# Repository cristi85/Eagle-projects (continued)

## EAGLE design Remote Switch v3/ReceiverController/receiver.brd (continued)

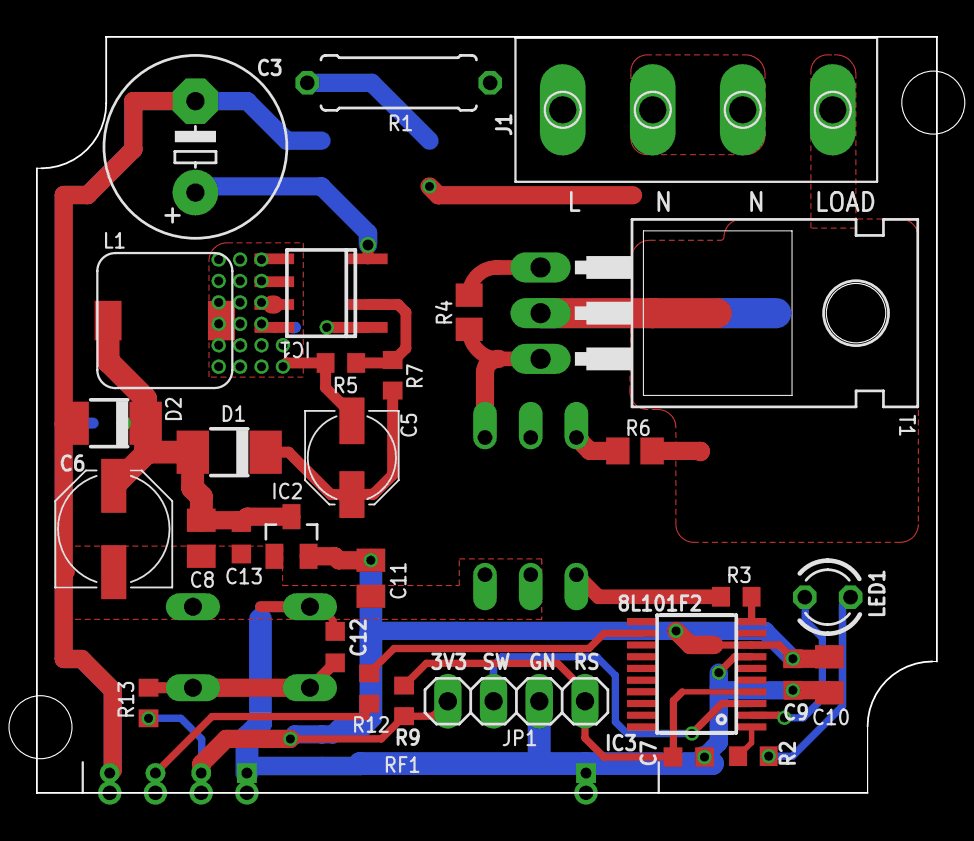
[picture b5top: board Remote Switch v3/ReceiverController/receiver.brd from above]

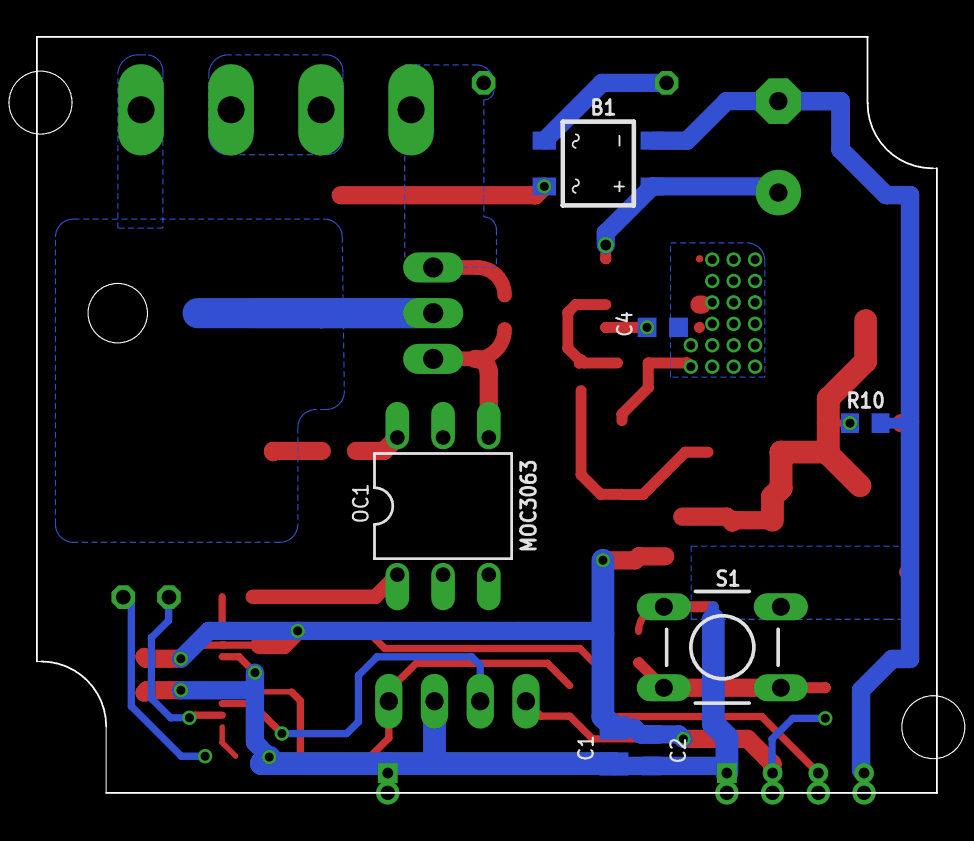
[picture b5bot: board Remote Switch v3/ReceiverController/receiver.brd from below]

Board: 2 copper layers, 50.0 x 42.0 mm, 38 parts (8 on the bottom side), 24 nets.

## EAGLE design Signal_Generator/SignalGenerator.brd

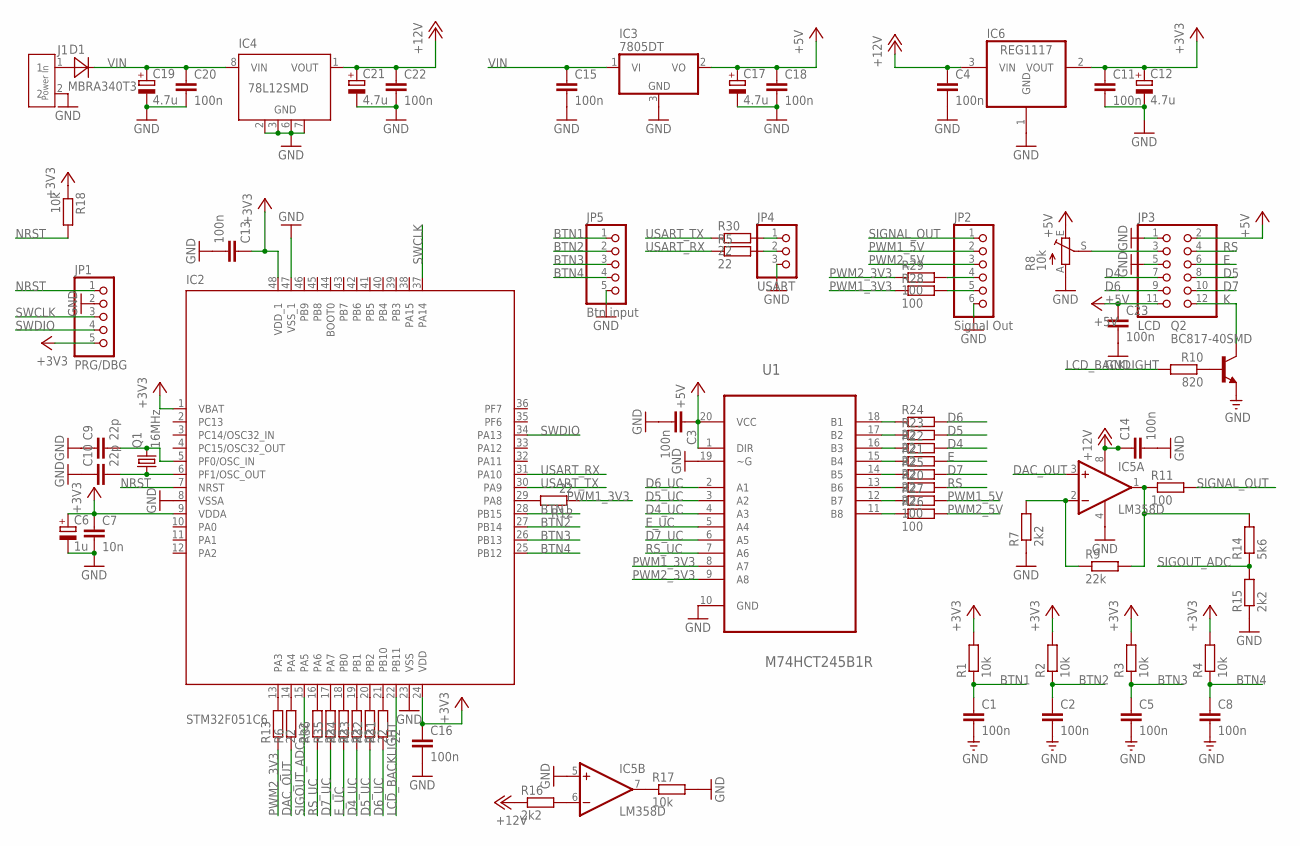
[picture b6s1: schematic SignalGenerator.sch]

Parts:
C1, C2, C3, C4, C5, C8, C11, C13, C14, C15, C16, C18, C20, C22, C23: 100n; C0805
C6: 1u; A/3216-18W
C7: 10n; C0805
C9, C10: 22p; C0603
C12, C21: 4.7u; PANASONIC_A
C17, C19: 4.7u; PANASONIC_B
D1: MBRA340T3; SMA
IC2: STM32F051C6; LQFP48-7X7
IC3: 7805DT; TO252
IC4: 78L12SMD; SO08
IC5: LM358D; SO08
IC6: REG1117; SOT223
J1: Power In; 2P-5.08
JP1: PRG/DBG; 1X05
JP2: Signal Out; 1X06
JP3: LCD; 2X06
JP4: USART; 1X03
JP5: Btn input; 1X05
Q1: 16MHz; SMD_CRYSTAL
Q2: BC817-40SMD; SOT23-BEC
R1, R2, R3, R4, R17, R18: 10k; R0603
R5, R12, R13, R20, R21, R22, R23, R24, R25, R30, R31, R32, R33, R34, R35, R36: 22; R0603
R6, R7, R15, R16: 2k2; R0603
R8: 10k; B25P
R9: 22k; R0603
R10: 820; R0603
R11, R26, R27, R28, R29: 100; R0603
R14: 5k6; R0603
U1: M74HCT245B1R; DIP254P762X393-20

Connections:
+3V3: C6.+, C7.1, C11.1, C12.+, C13.1, C16.1, IC2.1 (VBAT), IC2.9 (VDDA), IC2.24 (VDD), IC2.48 (VDD_1), IC6.2 (VOUT), JP1.5, R1.2, R2.2, R3.2, R4.2, R18.1
+5V: C3.1, C17.+, C18.1, C23.1, IC3.2 (VO), JP3.2, JP3.11, R8.E, U1.1 (DIR), U1.20 (VCC)
+12V: C4.1, C14.1, C21.+, C22.1, IC4.1 (VOUT), IC5.8 (V+), IC6.3 (VIN), R16.1
BTN1: C1.1, IC2.28 (PB15), JP5.1, R1.1
BTN2: C2.1, IC2.27 (PB14), JP5.2, R2.1
BTN3: C5.1, IC2.26 (PB13), JP5.3, R3.1
BTN4: C8.1, IC2.25 (PB12), JP5.4, R4.1
D4: JP3.7, R22.2
D4_UC: R33.1, U1.4 (A3)
D5: JP3.8, R23.2
D5_UC: R32.1, U1.3 (A2)
D6: JP3.9, R24.2
D6_UC: R31.1, U1.2 (A1)
D7: JP3.10, R25.2
D7_UC: R35.1, U1.6 (A5)
DAC_OUT: IC5.3 (+IN), R6.1
E: JP3.6, R21.2
E_UC: R34.1, U1.5 (A4)
GND: C1.2, C2.2, C3.2, C4.2, C5.2, C6.-, C7.2, C8.2, C9.1, C10.1, C11.2, C12.-, C13.2, C14.2, C15.2, C16.2, C17.-, C18.2, C19.-, C20.2, C21.-, C22.2, C23.2, IC2.8 (VSSA), IC2.23 (VSS), IC2.47 (VSS_1), IC3.3 (GND), IC4.2 (GND), IC4.3 (GND), IC4.6 (GND), IC4.7 (GND), IC5.4 (V-), IC5.5 (+IN), IC6.1 (GND), J1.2, JP1.2, JP2.6, JP3.1, JP3.5, JP4.3, JP5.5, Q2.E, R7.1, R8.A, R15.1, R17.2, U1.10 (GND), U1.19 (~G)
K: JP3.12, Q2.C
LCD_BACKLIGHT: IC2.22 (PB11), R10.2
unnamed: C10.2, IC2.6 (PF1/OSC_OUT), Q1.1
unnamed: C9.2, IC2.5 (PF0/OSC_IN), Q1.2
unnamed: JP3.3, R8.S
unnamed: Q2.B, R10.1
unnamed: IC5.2 (-IN), R7.2, R9.1
unnamed: IC2.14 (PA4), R6.2
unnamed: IC5.1 (OUT), R9.2, R11.1, R14.2
unnamed: IC2.29 (PA8), R12.2
unnamed: IC2.13 (PA3), R13.2
unnamed: JP2.5, R28.2
unnamed: JP2.4, R29.2
unnamed: IC2.16 (PA6), R36.2
unnamed: IC2.17 (PA7), R35.2
unnamed: IC2.18 (PB0), R34.2
unnamed: IC2.19 (PB1), R33.2
unnamed: R20.1, U1.13 (B6)
unnamed: R21.1, U1.15 (B4)
unnamed: R22.1, U1.16 (B3)
unnamed: R23.1, U1.17 (B2)
unnamed: R24.1, U1.18 (B1)
unnamed: R26.1, U1.11 (B8)
unnamed: R27.1, U1.12 (B7)
unnamed: R25.1, U1.14 (B5)
unnamed: JP4.1, R30.2
unnamed: JP4.2, R5.2
unnamed: IC2.20 (PB2), R32.2
unnamed: IC2.21 (PB10), R31.2
unnamed: D1.A, J1.1
unnamed: IC5.6 (-IN), R16.2
unnamed: IC5.7 (OUT), R17.1
NRST: IC2.7 (NRST), JP1.1, R18.2
PWM1_3V3: R12.1, R28.1, U1.8 (A7)
PWM1_5V: JP2.2, R27.2
PWM2_3V3: R13.1, R29.1, U1.9 (A8)
PWM2_5V: JP2.3, R26.2
RS: JP3.4, R20.2
RS_UC: R36.1, U1.7 (A6)
SIGNAL_OUT: JP2.1, R11.2
SIGOUT_ADC: IC2.15 (PA5), R14.1, R15.2
SWCLK: IC2.37 (PA14), JP1.3
SWDIO: IC2.34 (PA13), JP1.4
USART_RX: IC2.31 (PA10), R5.1
USART_TX: IC2.30 (PA9), R30.1
VIN: C15.1, C19.+, C20.1, D1.C, IC3.1 (VI), IC4.8 (VIN)

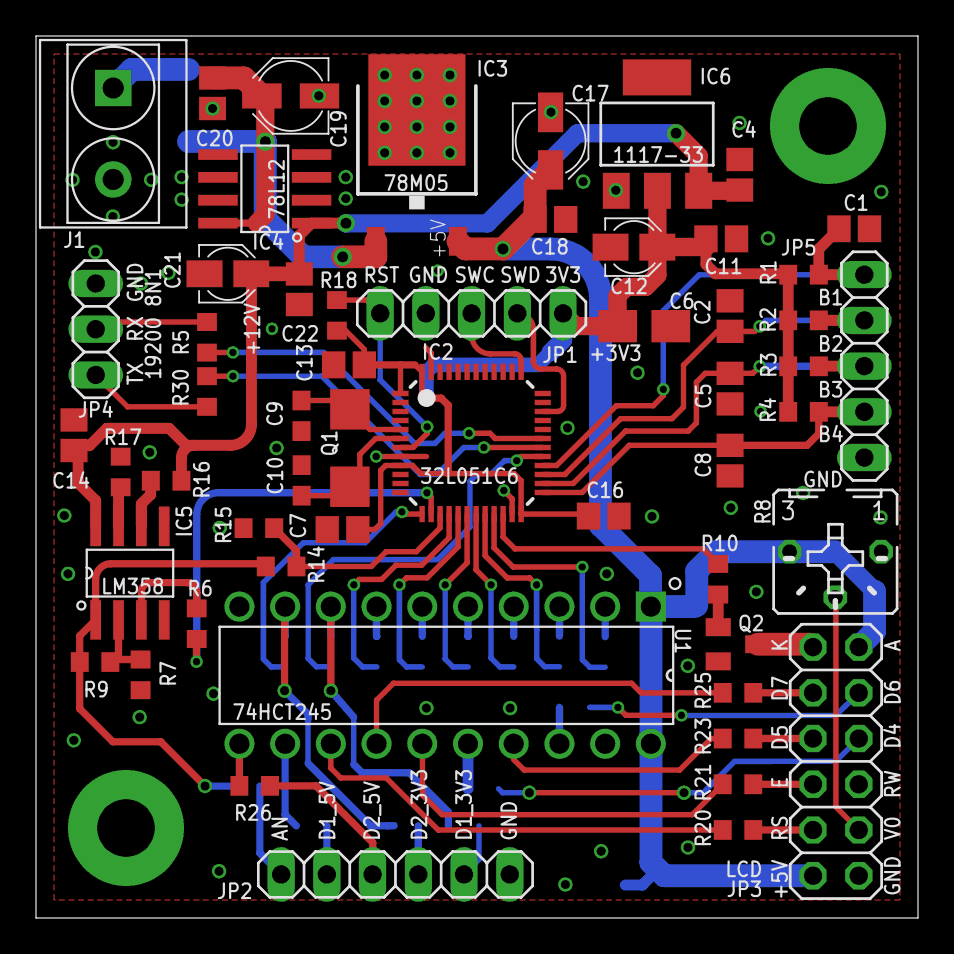
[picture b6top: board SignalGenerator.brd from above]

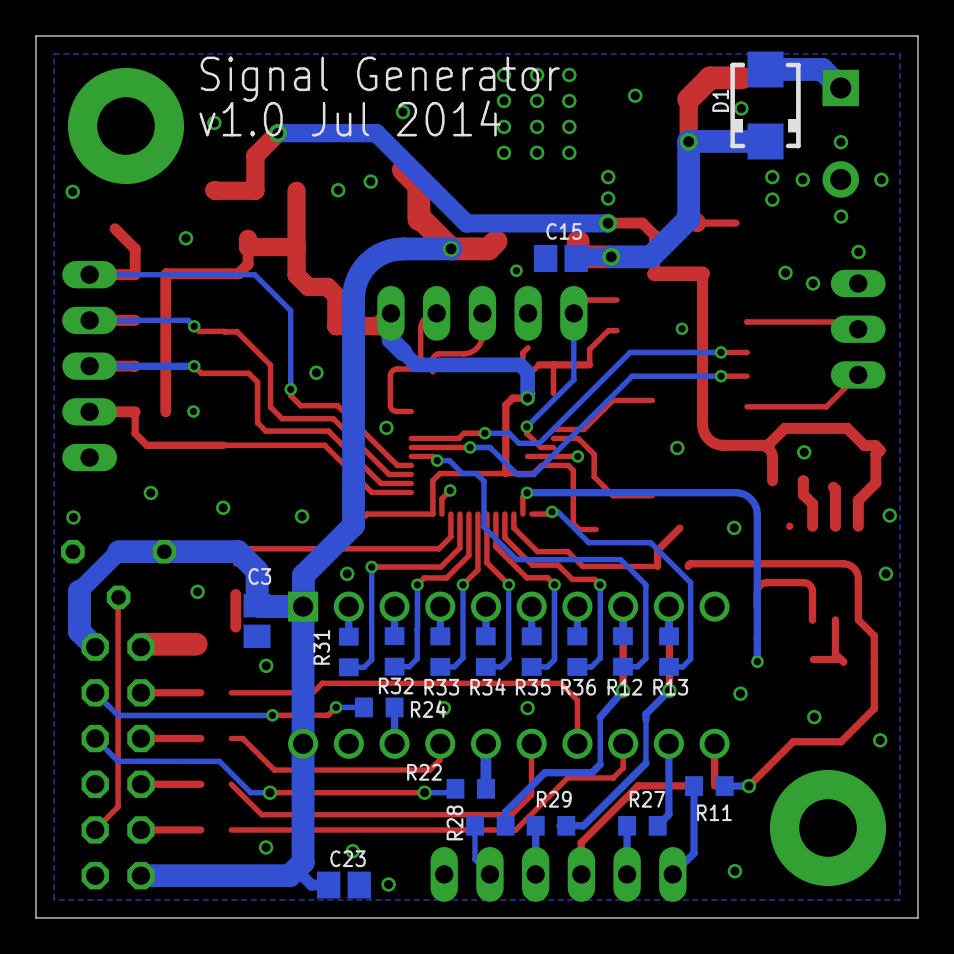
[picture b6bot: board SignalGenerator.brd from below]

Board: 2 copper layers, 49.0 x 49.0 mm, 73 parts (18 on the bottom side), 65 nets.

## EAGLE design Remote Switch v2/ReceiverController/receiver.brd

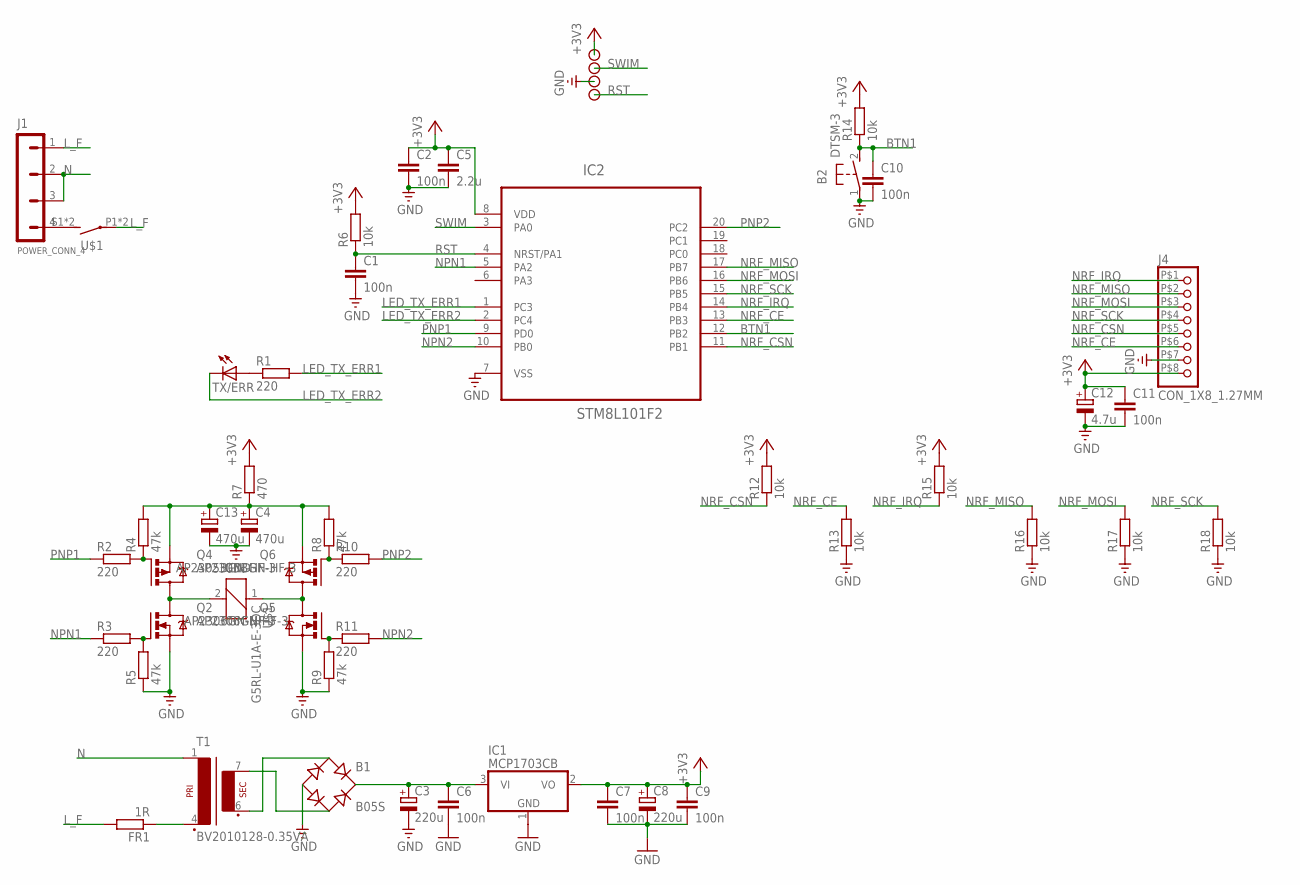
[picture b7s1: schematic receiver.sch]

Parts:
B1: B05S; MBS
B2: DTSM-3
C1, C2, C6, C7, C9, C10, C11: 100n; C0603K
C3: 220u; E3,5-8
C4, C13: 470u; E2,5-6
C5: 2.2u; C0805K
C8: 220u; E2,5-6
C12: 4.7u; SMC_A
FR1: 1R; 0309/10
IC1: MCP1703CB; SOT23
IC2: STM8L101F2; TSSOP20
J1: POWER_CONN_4; TERMINAL_BLOCK_4
J4: CON_1X8_1.27MM; CON_1X8PIN_1.27MM
Q2, Q5: AP2306GN-HF-3; SOT23
Q4, Q6: AP2305BGN-HF-3; SOT23
R1, R2, R3, R10, R11: 220; R0603
R4, R5, R8, R9: 47k; R0603
R6, R12, R13, R14, R15, R16, R17, R18: 10k; R0603
R7: 470; R0603
SIG_+3V1: CON_PAD; SMD_PAD
SIG_GND: CON_PAD; SMD_PAD
SIG_RST: CON_PAD; SMD_PAD
SIG_SWIM: CON_PAD; SMD_PAD
T1: BV2010128-0.35VA
TX/ERR: LED3MM
U$1: G5RL-U1A-E-3DC

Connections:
+3V3: C2.1, C5.1, C7.1, C8.+, C9.1, C11.1, C12.+, IC1.2 (VO), IC2.8 (VDD), J4.P$8 (8), R6.2, R7.2, R12.2, R14.2, R15.2, SIG_+3V1.P$1
BTN1: B2.2, C10.1, IC2.12 (PB2), R14.1
GND: B1.-, B2.1, C1.2, C2.2, C3.-, C4.-, C5.2, C6.2, C7.2, C8.-, C9.2, C10.2, C11.2, C12.-, C13.-, IC1.1 (GND), IC2.7 (VSS), J4.P$7 (7), Q2.2 (S), Q5.2 (S), R5.1, R9.1, R13.1, R16.1, R17.1, R18.1, SIG_GND.P$1
LED_TX_ERR1: IC2.1 (PC3), R1.2
LED_TX_ERR2: IC2.2 (PC4), TX/ERR.K (C)
L_F: FR1.2, J1.1, U$1.P1, U$1.P2
N: J1.2, J1.3, T1.1
unnamed: J1.4, U$1.S1 (S), U$1.S2 (S)
unnamed: R1.1, TX/ERR.A
unnamed: B1.AC2, T1.7 (S4)
unnamed: B1.+, C3.+, C6.1, IC1.3 (VI)
unnamed: B1.AC1, T1.6 (S3)
unnamed: Q2.1 (G), R3.2, R5.2
unnamed: Q2.3 (D), Q4.3 (D), U$1.2
unnamed: Q5.1 (G), R9.2, R11.1
unnamed: Q4.1 (G), R2.2, R4.1
unnamed: Q6.1 (G), R8.1, R10.1
unnamed: Q5.3 (D), Q6.3 (D), U$1.1
unnamed: C4.+, C13.+, Q4.2 (S), Q6.2 (S), R4.2, R7.1, R8.2
unnamed: FR1.1, T1.4 (P2)
NPN1: IC2.5 (PA2), R3.1
NPN2: IC2.10 (PB0), R11.2
NRF_CE: IC2.13 (PB3), J4.P$6 (6), R13.2
NRF_CSN: IC2.11 (PB1), J4.P$5 (5), R12.1
NRF_IRQ: IC2.14 (PB4), J4.P$1 (1), R15.1
NRF_MISO: IC2.17 (PB7), J4.P$2 (2), R16.2
NRF_MOSI: IC2.16 (PB6), J4.P$3 (3), R17.2
NRF_SCK: IC2.15 (PB5), J4.P$4 (4), R18.2
PNP1: IC2.9 (PD0), R2.1
PNP2: IC2.20 (PC2), R10.2
RST: C1.1, IC2.4 (NRST/PA1), R6.1, SIG_RST.P$1
SWIM: IC2.3 (PA0), SIG_SWIM.P$1

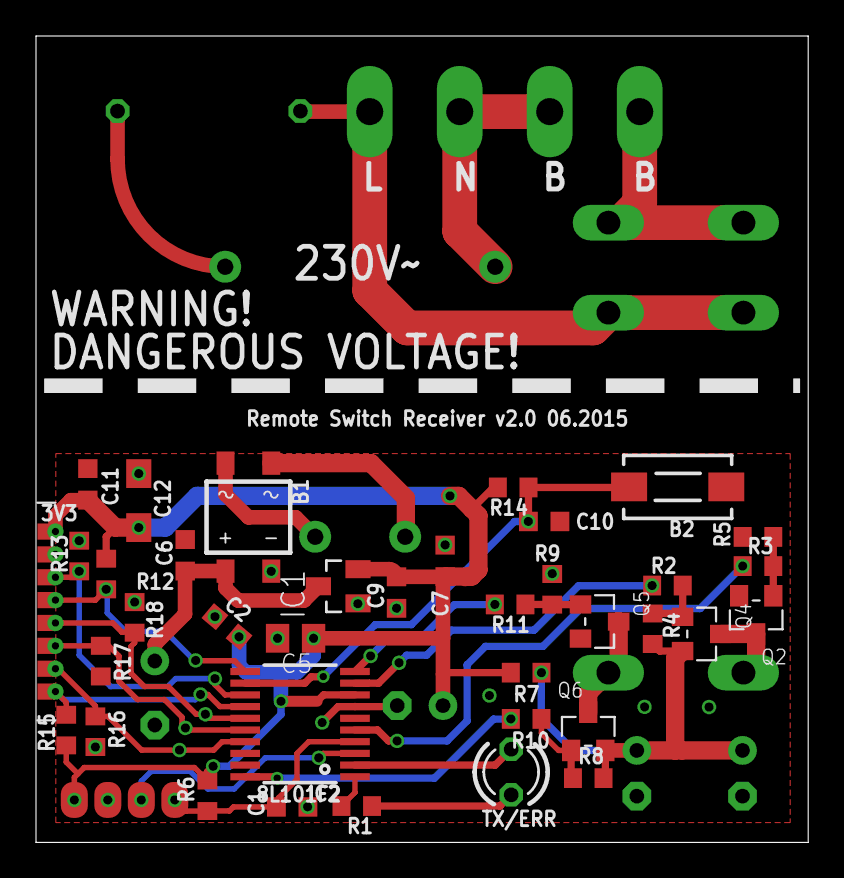
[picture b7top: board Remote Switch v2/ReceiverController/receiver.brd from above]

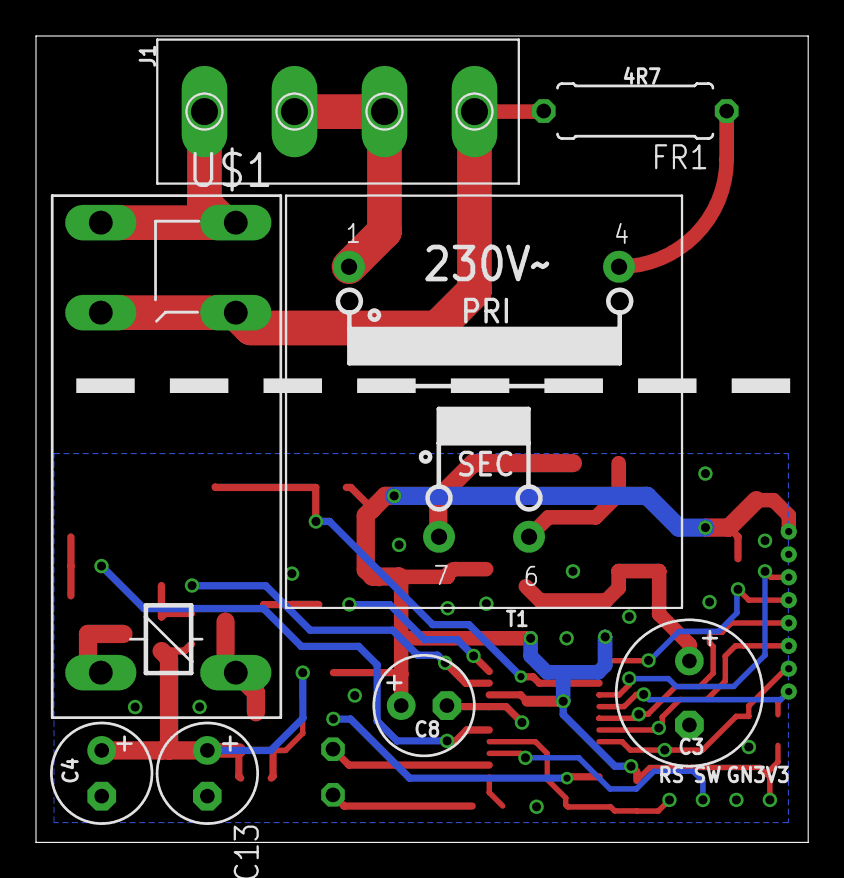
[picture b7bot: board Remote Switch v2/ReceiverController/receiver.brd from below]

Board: 2 copper layers, 42.9 x 44.8 mm, 49 parts (8 on the bottom side), 32 nets.

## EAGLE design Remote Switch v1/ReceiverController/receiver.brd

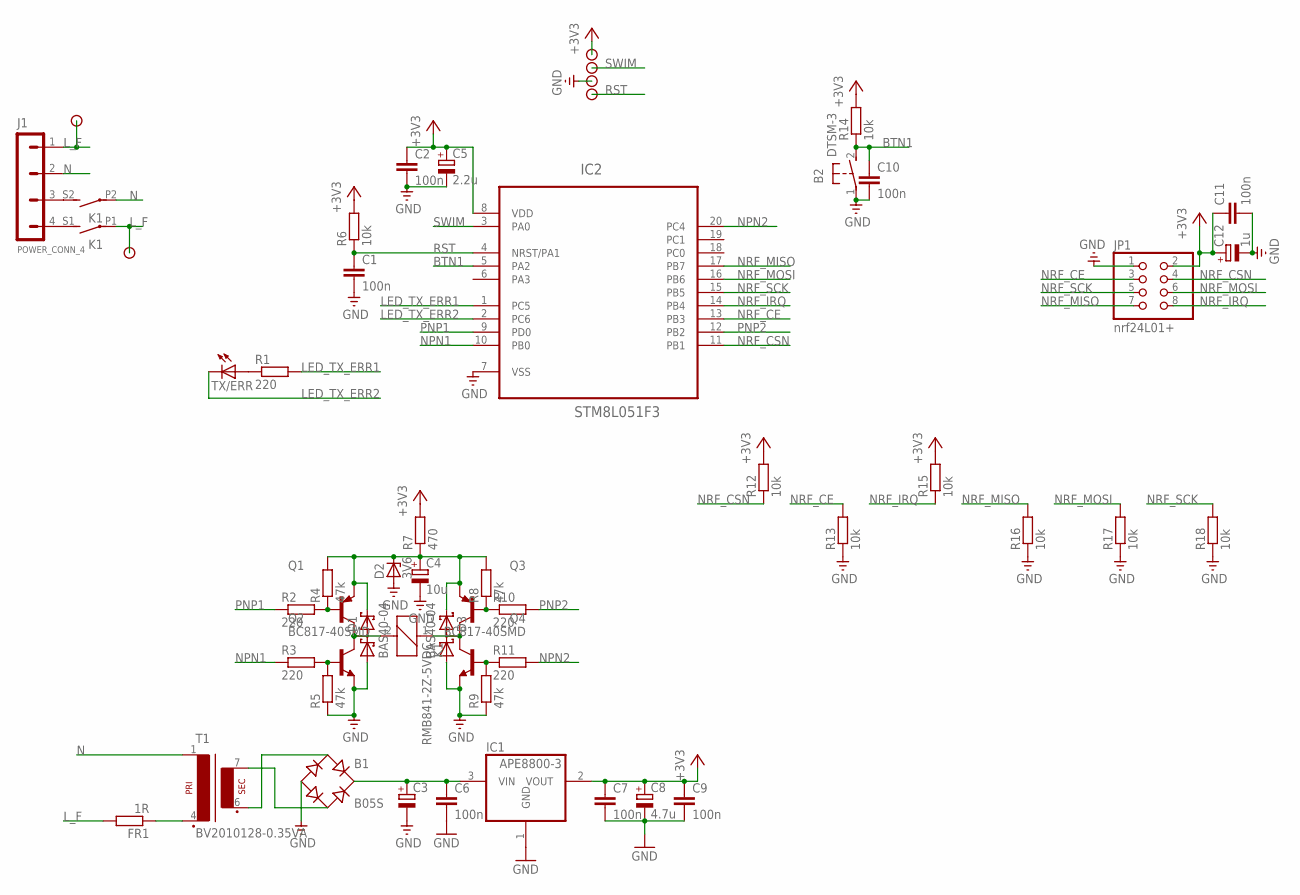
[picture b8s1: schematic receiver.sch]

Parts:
B1: B05S; MBS
B2: DTSM-3
C1, C2, C6, C7, C9, C10, C11: 100n; C0603K
C3: CPOL-EUSMCB; SMC_B
C4: 10u; SMC_B
C5: 2.2u; SMC_A
C8: 4.7u; SMC_A
C12: 1u; SMC_A
D1, D3: BAS40-04; SOT23
D2: 3V6; SOT23
FR1: 1R; 0309/10
IC1: APE8800-3; SOT23
IC2: STM8L051F3; TSSOP20
J1: POWER_CONN_4; TERMINAL_BLOCK_4
J2, J3: CON_PAD_THICK_WIRE; SMD_PAD_THICK_WIRE
JP1: nrf24L01+; 2X04
K1: RMB841-2Z-5VDC
Q1, Q3: BC807-40-PNP-SOT23-BEC; SOT23-BEC
Q2, Q4: BC817-40SMD; SOT23-BEC
R1, R2, R3, R10, R11: 220; R0603
R4, R5, R8, R9: 47k; R0603
R6, R12, R13, R14, R15, R16, R17, R18: 10k; R0603
R7: 470; R0603
SIG_+3V1: CON_PAD; SMD_PAD
SIG_GND: CON_PAD; SMD_PAD
SIG_RST: CON_PAD; SMD_PAD
SIG_SWIM: CON_PAD; SMD_PAD
T1: BV2010128-0.35VA
TX/ERR: LED3MM

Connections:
+3V3: C2.1, C5.+, C7.1, C8.+, C9.1, C11.1, C12.+, IC1.2 (VOUT), IC2.8 (VDD), JP1.2, R6.2, R7.2, R12.2, R14.2, R15.2, SIG_+3V1.P$1
BTN1: B2.2, C10.1, IC2.5 (PA2), R14.1
GND: B1.-, B2.1, C1.2, C2.2, C3.-, C4.-, C5.-, C6.2, C7.2, C8.-, C9.2, C10.2, C11.2, C12.-, D1.1 (A1), D2.1 (A), D3.1 (A1), IC1.1 (GND), IC2.7 (VSS), JP1.1, Q2.E, Q4.E, R5.1, R9.1, R13.1, R16.1, R17.1, R18.1, SIG_GND.P$1
LED_TX_ERR1: IC2.1 (PC5), R1.2
LED_TX_ERR2: IC2.2 (PC6), TX/ERR.K (C)
L_F: FR1.2, J1.1, J2.P$1, J3.P$1, K1.P1
N: J1.2, K1.P2, T1.1
unnamed: R1.1, TX/ERR.A
unnamed: B1.AC2, T1.7 (S4)
unnamed: B1.+, C3.+, C6.1, IC1.3 (VIN)
unnamed: B1.AC1, T1.6 (S3)
unnamed: Q2.B, R3.2, R5.2
unnamed: D1.3 (C1A2), K1.2, Q1.C, Q2.C
unnamed: Q4.B, R9.2, R11.1
unnamed: Q1.B, R2.2, R4.1
unnamed: Q3.B, R8.1, R10.1
unnamed: J1.4, K1.S1 (S)
unnamed: J1.3, K1.S2 (S)
unnamed: D3.3 (C1A2), K1.1, Q3.C, Q4.C
unnamed: C4.+, D1.2 (C2), D2.3 (C), D3.2 (C2), Q1.E, Q3.E, R4.2, R7.1, R8.2
unnamed: FR1.1, T1.4 (P2)
NPN1: IC2.10 (PB0), R3.1
NPN2: IC2.20 (PC4), R11.2
NRF_CE: IC2.13 (PB3), JP1.3, R13.2
NRF_CSN: IC2.11 (PB1), JP1.4, R12.1
NRF_IRQ: IC2.14 (PB4), JP1.8, R15.1
NRF_MISO: IC2.17 (PB7), JP1.7, R16.2
NRF_MOSI: IC2.16 (PB6), JP1.6, R17.2
NRF_SCK: IC2.15 (PB5), JP1.5, R18.2
PNP1: IC2.9 (PD0), R2.1
PNP2: IC2.12 (PB2), R10.2
RST: C1.1, IC2.4 (NRST/PA1), R6.1, SIG_RST.P$1
SWIM: IC2.3 (PA0), SIG_SWIM.P$1

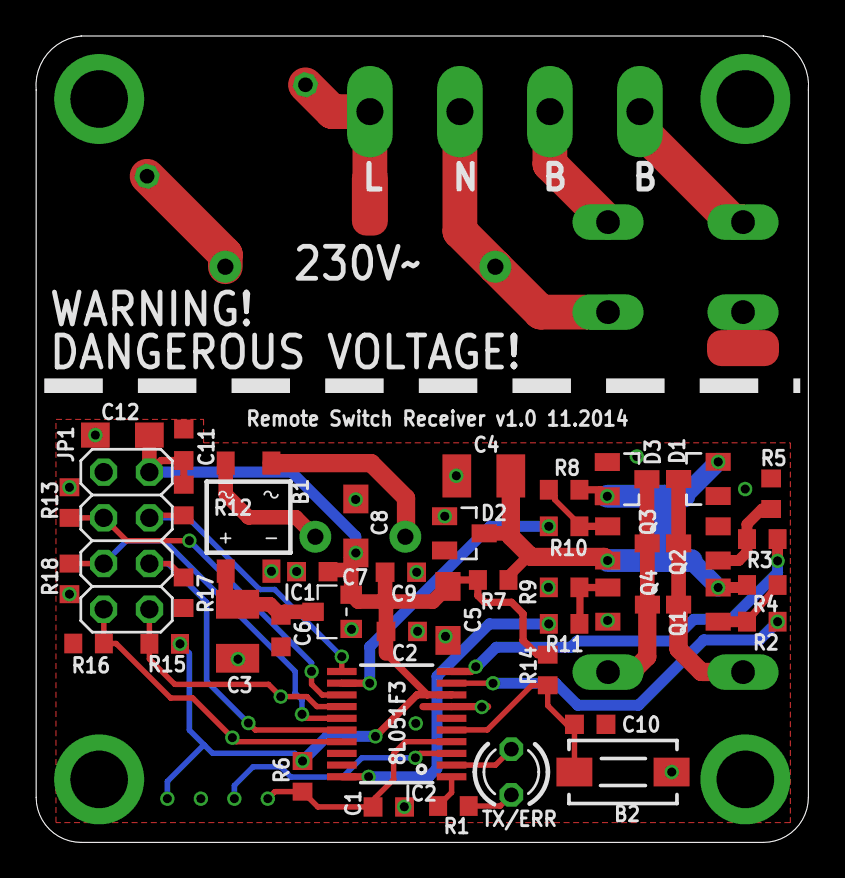
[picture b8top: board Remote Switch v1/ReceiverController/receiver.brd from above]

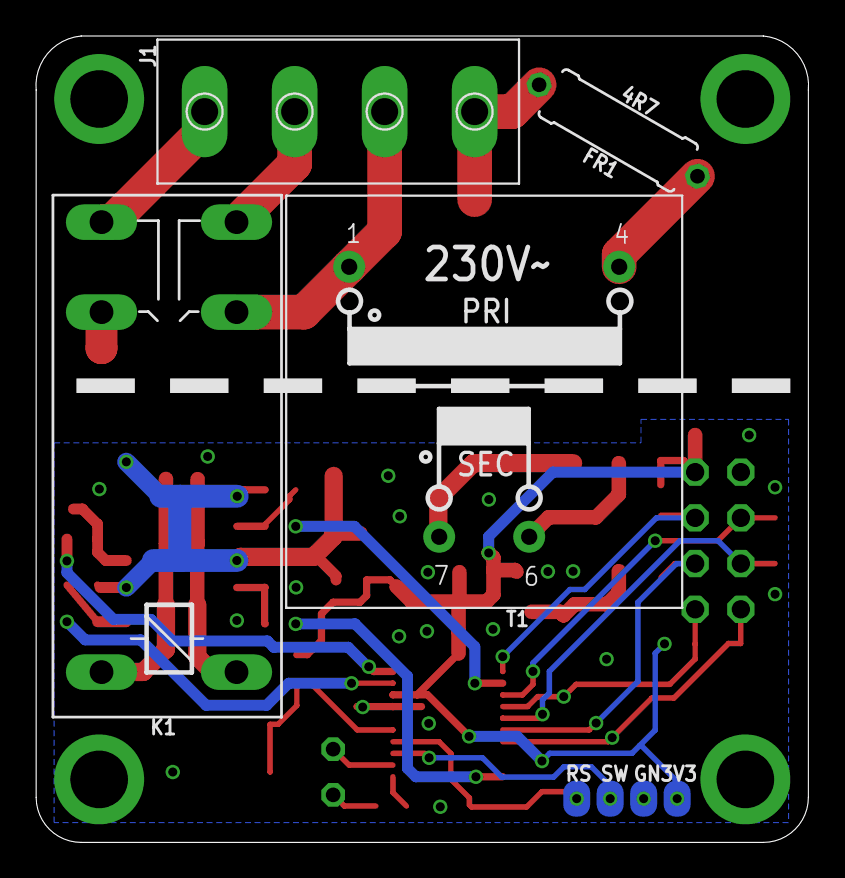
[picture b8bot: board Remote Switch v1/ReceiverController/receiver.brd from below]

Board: 2 copper layers, 42.9 x 44.8 mm, 53 parts (8 on the bottom side), 33 nets.

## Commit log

2015-07-12 :tada: Added .gitattributes & .gitignore files
2015-07-12 Add Remote Switch v3 project
2015-07-12 Add Remote Switch v1 project
2015-07-12 Add Remote Switch v2 project
2015-07-12 Add Signal Generator project
2015-07-13 PCB work
2015-09-12 PCB work for Remote Switch
2016-01-04 Add Remote Switch v3.1
    Add Remote Switch v3.1
2016-01-13 PCB work - almost complete
2016-01-17 PCB work
    PCB TODO list work
2016-02-09 Add Wireless Node PCB project
2016-02-19 PCB Work, finished, final review needed
2016-02-20 PCB work, almost done
2016-03-04 PCB work, finished
2016-03-08 Split project into Relay and Triac based wireless node
2016-03-09 Ready for production
